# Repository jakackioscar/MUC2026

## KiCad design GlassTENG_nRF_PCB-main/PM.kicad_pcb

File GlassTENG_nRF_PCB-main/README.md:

# GlassTENG nRF5340 PCB
Currently a work-in-progress

## Components
- nRF5340-QKXX
- ...

## References
- [nRF5340 Reference Circuitry Config. 1](https://docs.nordicsemi.com/r/bundle/ps_nrf5340/page/chapters/ref_circuitry.html)

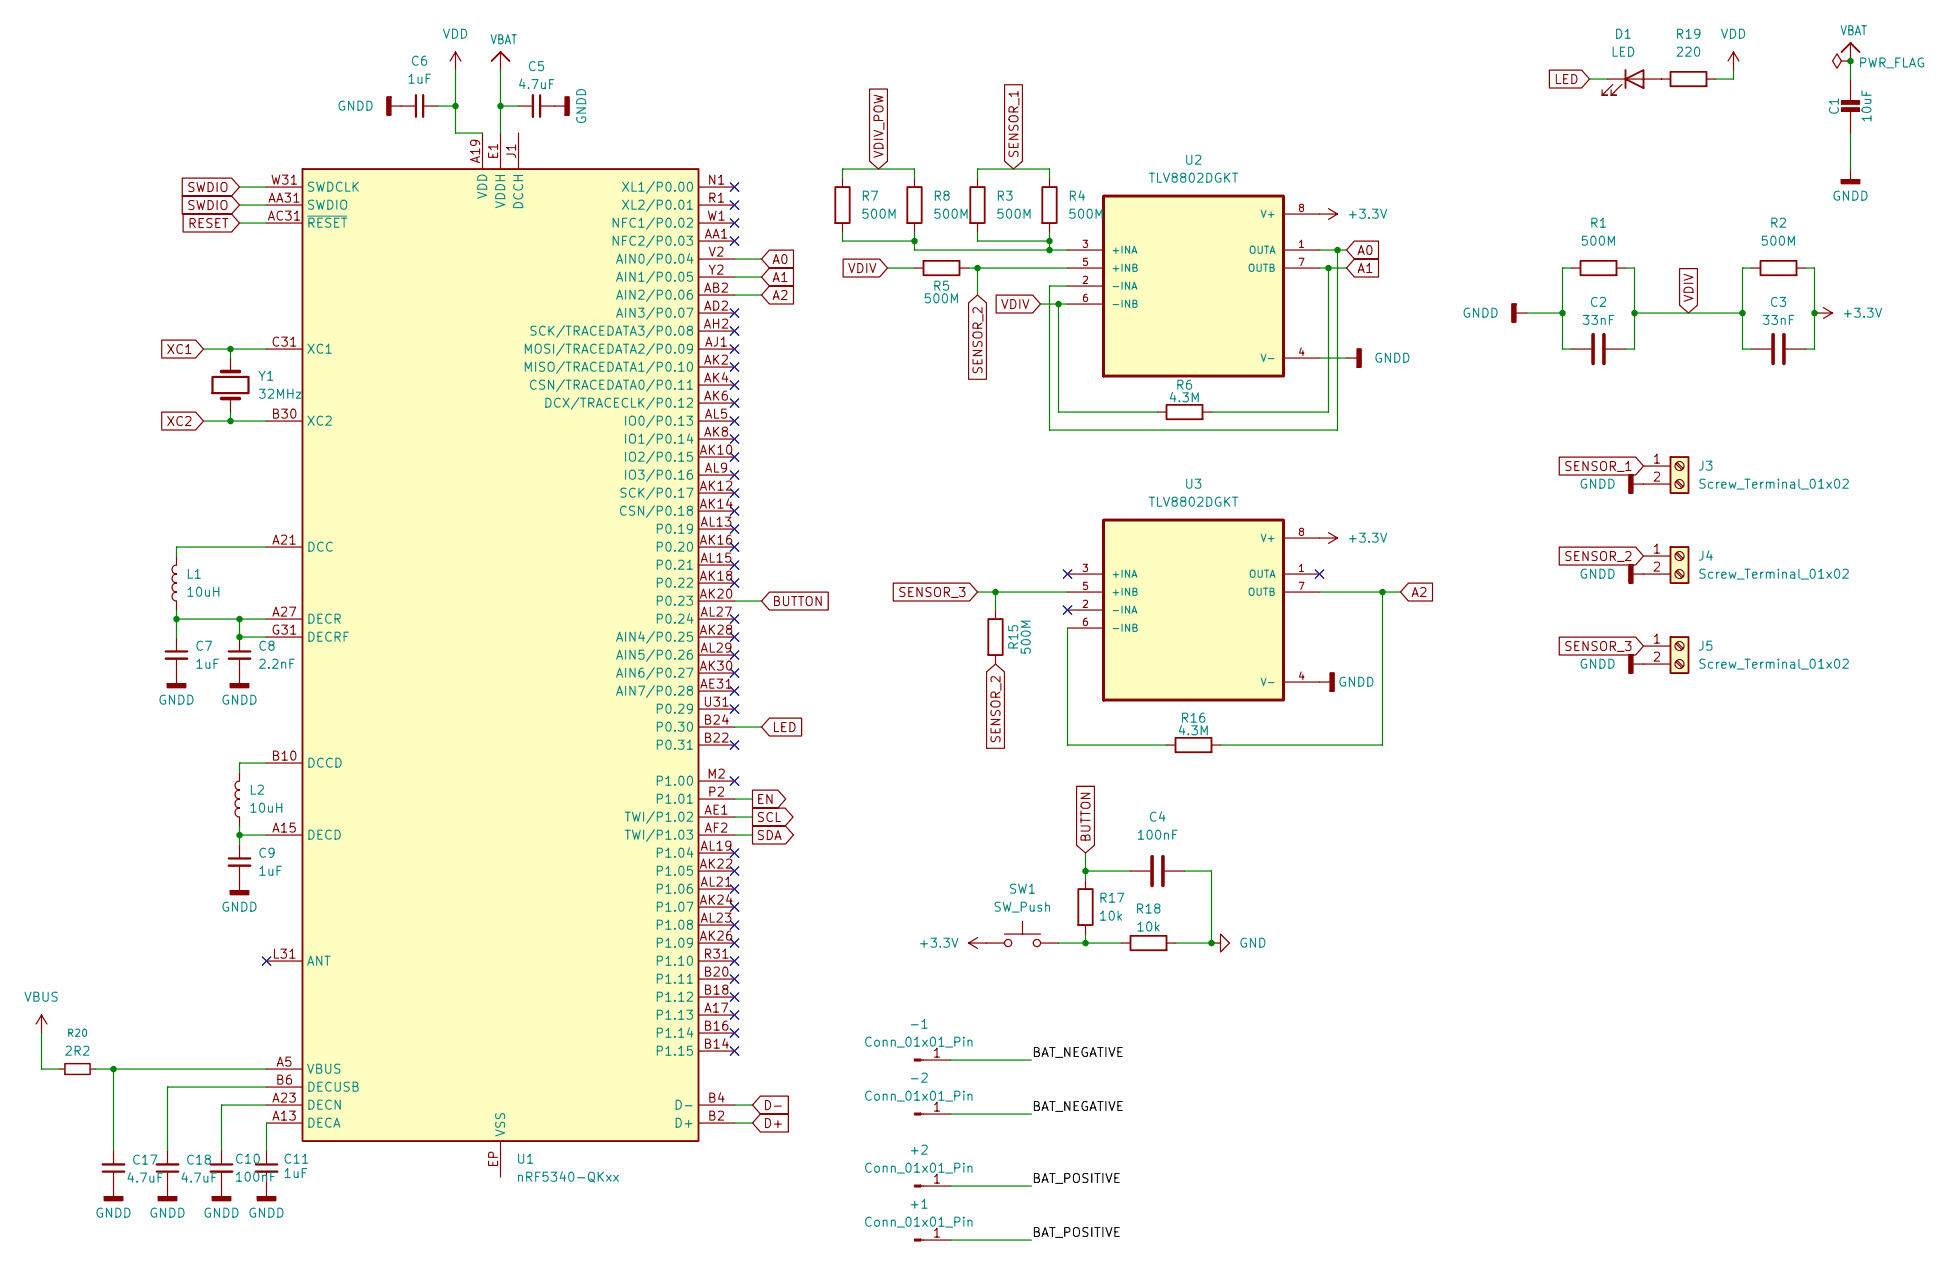
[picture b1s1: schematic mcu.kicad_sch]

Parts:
+1, +2: Conn_01x01_Pin; SolderWirePad_1x01_SMD_1.5x3mm
-1, -2: Conn_01x01_Pin; SolderWirePad_1x01_SMD_1.5x3mm
C1: 10uF; C_0805_2012Metric_Pad1.18x1.45mm_HandSolder
C2, C3: 33nF; C_0805_2012Metric_Pad1.18x1.45mm_HandSolder
C4, C10: 100nF; C_0805_2012Metric_Pad1.18x1.45mm_HandSolder
C5, C17, C18: 4.7uF; C_0805_2012Metric_Pad1.18x1.45mm_HandSolder
C6, C7, C9, C11: 1uF; C_0805_2012Metric_Pad1.18x1.45mm_HandSolder
C8: 2.2nF; C_0805_2012Metric_Pad1.18x1.45mm_HandSolder
D1: LED; LED_0805_2012Metric_Pad1.15x1.40mm_HandSolder
J3, J4, J5: Screw_Terminal_01x02; TerminalBlock_Phoenix_PT-1,5-2-5.0-H_1x02_P5.00mm_Horizontal
L1, L2: 10uH; L_0805_2012Metric_Pad1.05x1.20mm_HandSolder
R1, R2, R3, R4, R5, R7, R8, R15: 500M; R_0805_2012Metric
R6, R16: 4.3M; R_0805_2012Metric
R17, R18: 10k; R_0805_2012Metric
R19: 220; R_0805_2012Metric
R20: 2R2; R_0805_2012Metric
SW1: SW_Push; SW_PUSH_6mm_H4.3mm
U1: nRF5340-QKxx; Nordic_AQFN-94-1EP_7x7mm_P0.4mm
U2, U3: TLV8802DGKT; VSSOP-8_3x3mm_P0.65mm
Y1: 32MHz; Crystal_SMD_3215-2Pin_3.2x1.5mm

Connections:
+3.3V: C3.1, R2.2, SW1.1, U2.8 (V+), U3.8 (V+)
/MCU/BAT_NEGATIVE: -1.1 (Pin_1_1), -2.1 (Pin_1_1)
/MCU/BAT_POSITIVE: +1.1 (Pin_1_1), +2.1 (Pin_1_1)
A0: U1.V2 (AIN0/P0.04), U2.1 (OUTA), U2.2 (-INA)
A1: R6.2, U1.Y2 (AIN1/P0.05), U2.7 (OUTB)
A2: R16.2, U1.AB2 (AIN2/P0.06), U3.7 (OUTB)
BUTTON: C4.1, R17.1, U1.AK20 (P0.23)
D+: U1.B2 (D+); also elsewhere on the board
D-: U1.B4 (D-); also elsewhere on the board
EN: U1.P2 (P1.01); also elsewhere on the board
GND: C4.2, R18.2; also elsewhere on the board
GNDD: C1.2, C2.2, C5.1, C6.1, C7.2, C8.2, C9.2, C10.2, C11.2, C17.1, C18.1, J3.2, J4.2, J5.2, R1.1, U2.4 (V-), U3.4 (V-); also elsewhere on the board
LED: D1.1 (K), U1.B24 (P0.30)
unnamed: D1.2 (A), R19.1
unnamed: R17.2, R18.1, SW1.2
unnamed: L1.2, U1.A21 (DCC)
unnamed: L2.2, U1.B10 (DCCD)
unnamed: C11.1, U1.A13 (DECA)
unnamed: C9.1, L2.1, U1.A15 (DECD)
unnamed: C10.1, U1.A23 (DECN)
unnamed: C7.1, C8.1, L1.1, U1.A27 (DECR), U1.G31 (DECRF)
unnamed: C18.2, U1.B6 (DECUSB)
unnamed: C17.2, R20.2, U1.A5 (VBUS)
unnamed: R3.2, R4.2, R7.2, R8.2, U2.3 (+INA)
unnamed: R16.1, U3.6 (-INB)
RESET: U1.AC31 (~RESET)
SCL: U1.AE1 (TWI/P1.02); also elsewhere on the board
SDA: U1.AF2 (TWI/P1.03); also elsewhere on the board
SENSOR_1: J3.1, R3.1, R4.1
SENSOR_2: J4.1, R5.1, R15.2, U2.5 (+INB)
SENSOR_3: J5.1, R15.1, U3.5 (+INB)
SWDIO: U1.AA31 (SWDIO), U1.W31 (SWDCLK)
VBAT: C1.1, C5.2, U1.E1 (VDDH); also elsewhere on the board
VBUS: R20.1; also elsewhere on the board
VDD: C6.2, R19.2, U1.A19 (VDD), U1.AC1 (VDD), U1.AG1 (VDD), U1.AJ31 (VDD), U1.AL3 (VDD), U1.AL7 (VDD), U1.AL11 (VDD), U1.AL17 (VDD), U1.AL25 (VDD), U1.B8 (VDD), U1.B28 (VDD), U1.C1 (VDD), U1.E31 (VDD), U1.L1 (VDD), U1.N31 (VDD), U1.U1 (VDD)
VDIV: C2.1, C3.2, R1.2, R2.1, R5.2, R6.1, U2.6 (-INB)
VDIV_POW: R7.1, R8.1
XC1: U1.C31 (XC1), Y1.2
XC2: U1.B30 (XC2), Y1.1

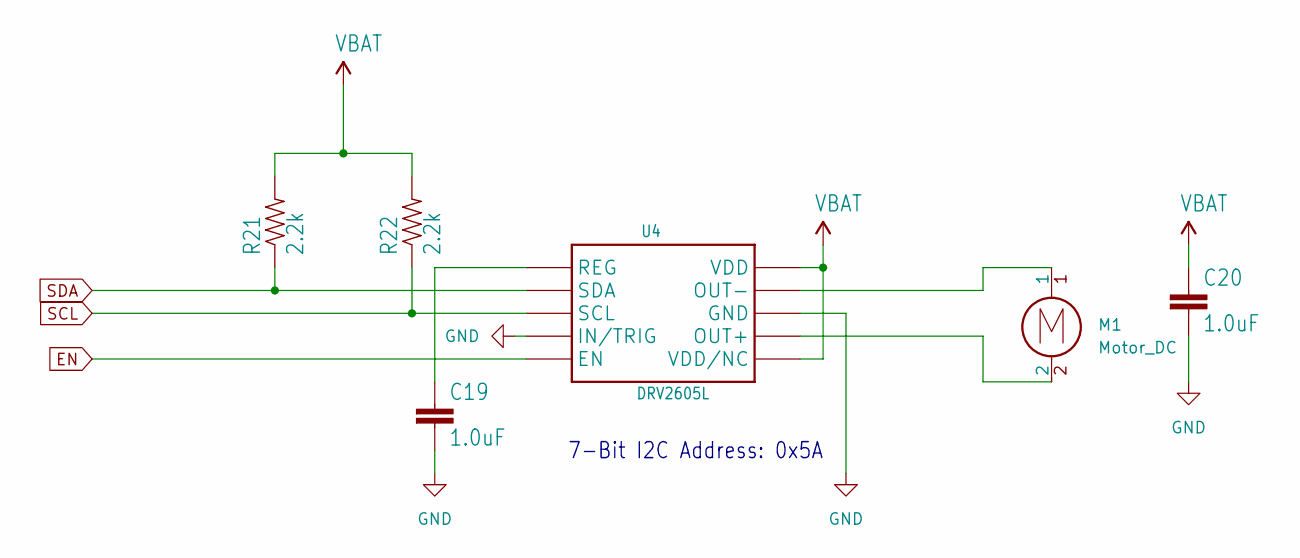
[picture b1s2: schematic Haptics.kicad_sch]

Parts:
C19, C20: 1.0uF; C_0805_2012Metric_Pad1.18x1.45mm_HandSolder
M1: Motor_DC; JST_PH_B2B-PH-SM4-TB_1x02-1MP_P2.00mm_Vertical
R21, R22: 2.2k; R_0805_2012Metric
U4: DRV2605L; MSOP-10_3x3mm_P0.5mm

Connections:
EN: U4.5 (EN); also elsewhere on the board
GND: C19.2, C20.2, U4.4 (IN/TRIG), U4.8 (GND); also elsewhere on the board
unnamed: M1.2, U4.7 (OUT+)
unnamed: M1.1, U4.9 (OUT-)
unnamed: C19.1, U4.1 (REG)
SCL: R22.1, U4.2 (SCL); also elsewhere on the board
SDA: R21.1, U4.3 (SDA); also elsewhere on the board
VBAT: C20.1, R21.2, R22.2, U4.6 (VDD/NC), U4.10 (VDD); also elsewhere on the board

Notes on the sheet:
7-Bit I2C Address: 0x5A

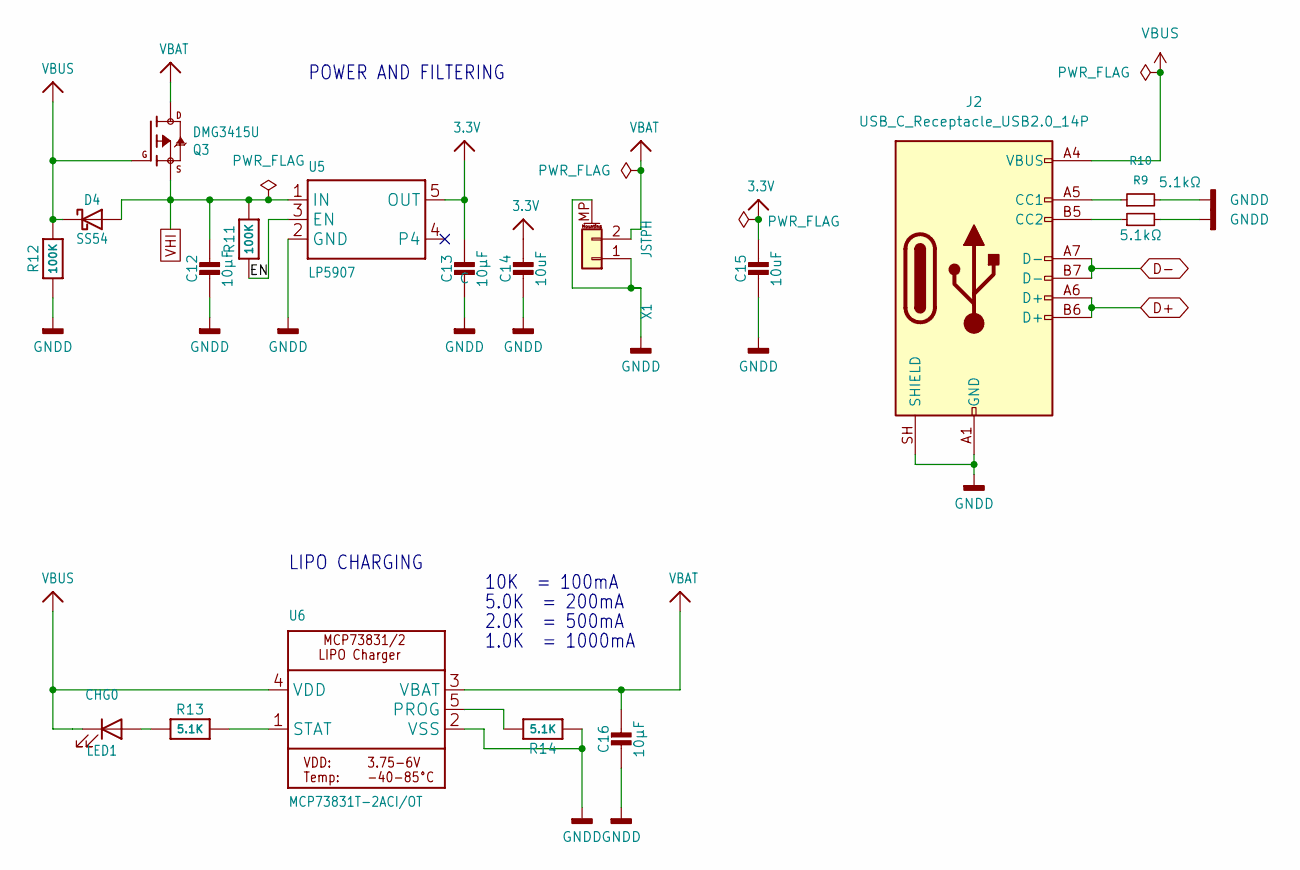
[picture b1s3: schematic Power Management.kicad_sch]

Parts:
C12, C13, C16: 10µF; C_0805_2012Metric_Pad1.18x1.45mm_HandSolder
C14, C15: 10uF; C_0805_2012Metric_Pad1.18x1.45mm_HandSolder
CHG0: LED1; LED_0805_2012Metric_Pad1.15x1.40mm_HandSolder
D4: SS54; D_SMA
J2: USB_C_Receptacle_USB2.0_14P; USB_C_Receptacle_GCT_USB4105-xx-A_16P_TopMnt_Horizontal
Q3: DMG3415U; SOT-23
R9, R10: 5.1kΩ; R_0805_2012Metric
R11, R12: 100K; R_0805_2012Metric
R13, R14: 5.1K; R_0805_2012Metric
U5: LP5907; SOT-23-5_HandSoldering
U6: MCP73831T-2ACI/OT; SOT-23-5_HandSoldering
X1: JSTPH; JST_PH_S2B-PH-SM4-TB_1x02-1MP_P2.00mm_Horizontal

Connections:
3.3V: C13.1, C14.1, C15.1, U5.5 (OUT)
/Power Management/EN: R11.1, U5.3 (EN)
D+: J2.A6 (D+), J2.B6 (D+); also elsewhere on the board
D-: J2.A7 (D-), J2.B7 (D-); also elsewhere on the board
GNDD: C12.2, C13.2, C14.2, C15.2, C16.2, J2.A1 (GND), J2.A12 (GND), J2.B1 (GND), J2.B12 (GND), J2.SH (SHIELD), R9.2, R10.2, R12.1, R14.1, U5.2 (GND), U6.2 (VSS), X1.1, X1.MP (MountPin); also elsewhere on the board
unnamed: CHG0.2 (A), R13.1
unnamed: J2.A5 (CC1), R10.1
unnamed: J2.B5 (CC2), R9.1
unnamed: R14.2, U6.5 (PROG)
unnamed: R13.2, U6.1 (STAT)
VBAT: C16.1, Q3.3 (D), U6.3 (VBAT), X1.2; also elsewhere on the board
VBUS: CHG0.1 (K), D4.1 (K), J2.A4 (VBUS), J2.A9 (VBUS), J2.B4 (VBUS), J2.B9 (VBUS), Q3.1 (G), R12.2, U6.4 (VDD); also elsewhere on the board
VHI: C12.1, D4.2 (A), Q3.2 (S), R11.2, U5.1 (IN)

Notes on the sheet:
2.0K = 500mA
LIPO CHARGING
POWER AND FILTERING
1.0K = 1000mA
10K = 100mA
5.0K = 200mA

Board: 2 copper layers, 66 parts (0 on the bottom side), 49 nets, no tracks yet.
